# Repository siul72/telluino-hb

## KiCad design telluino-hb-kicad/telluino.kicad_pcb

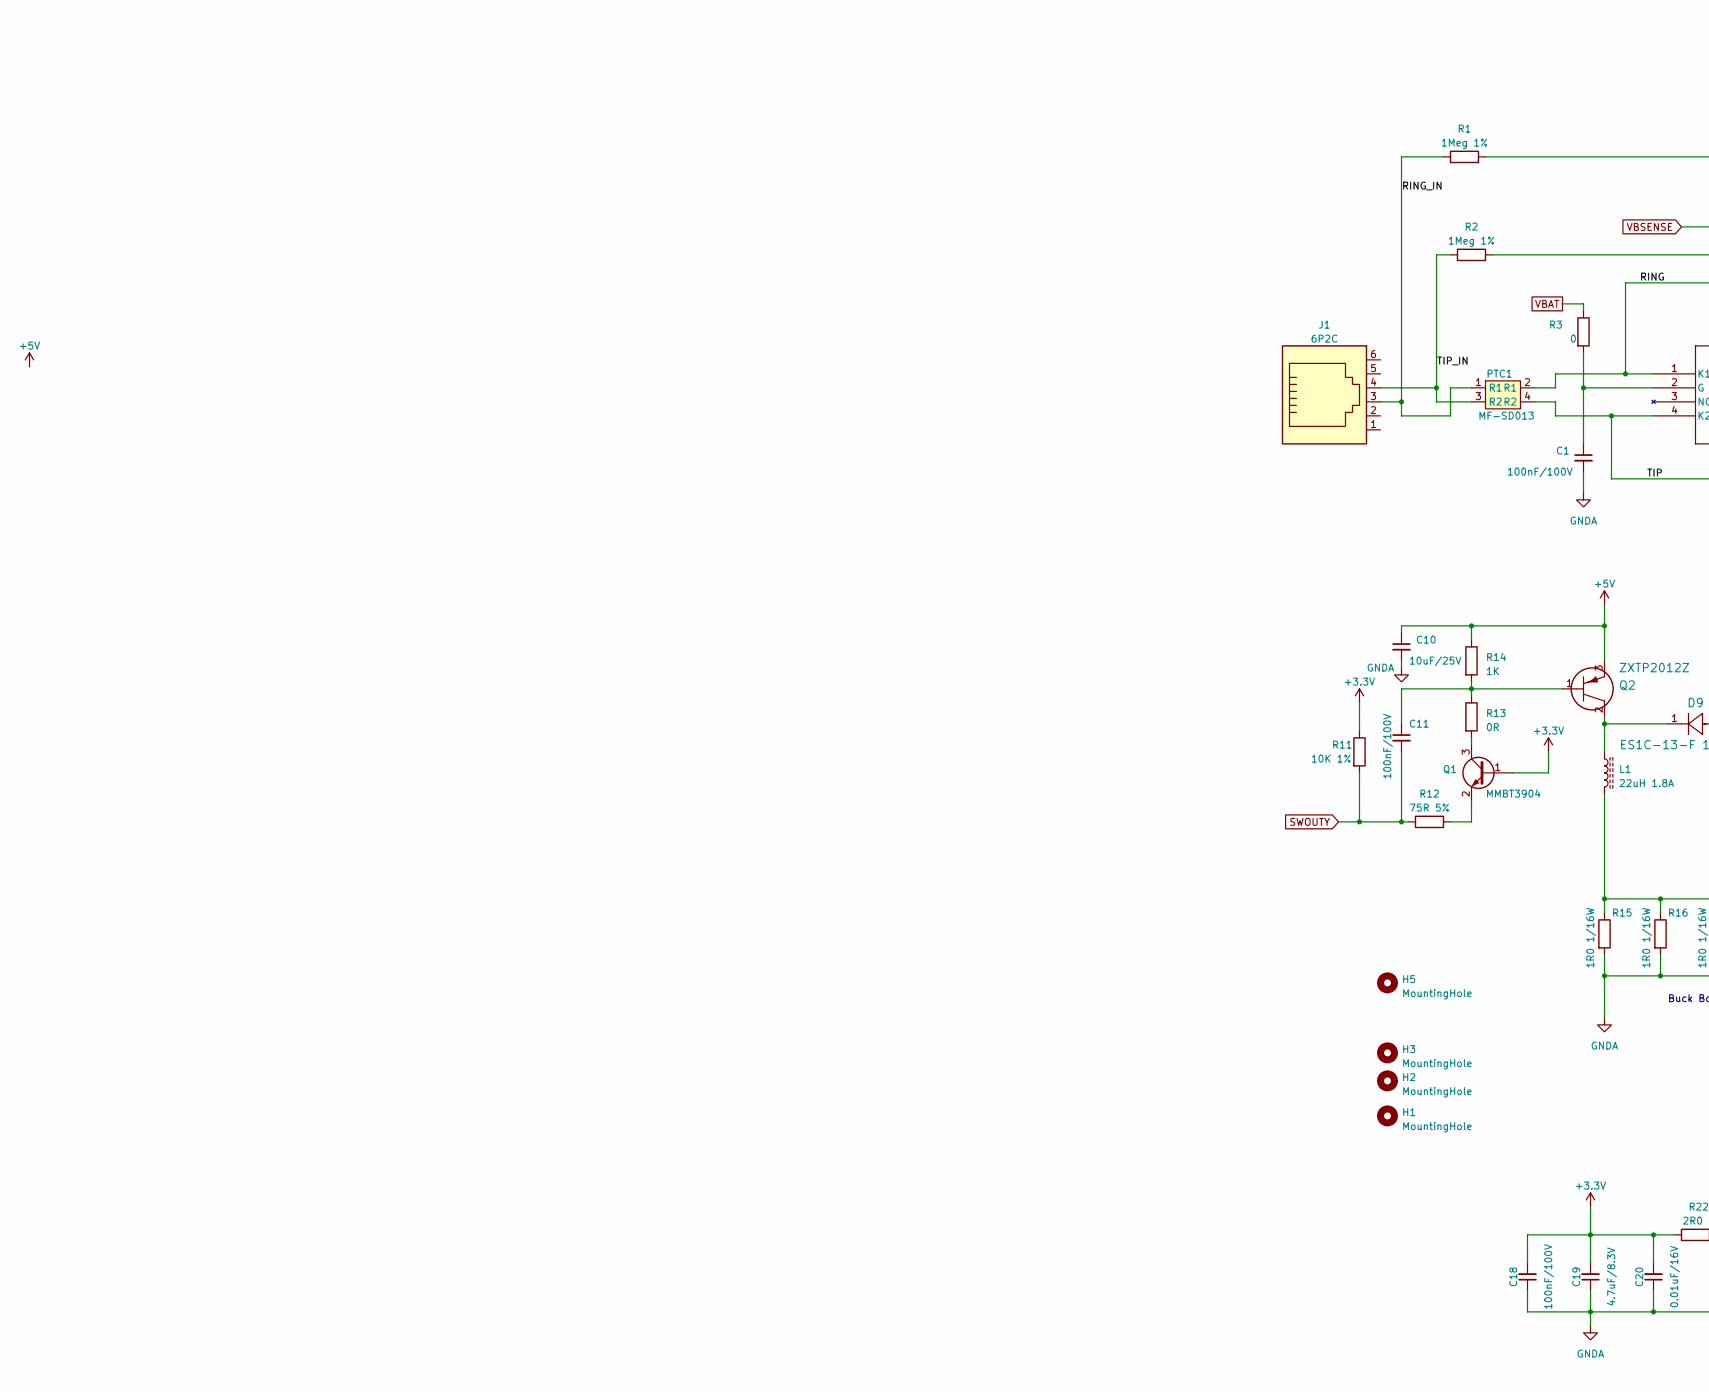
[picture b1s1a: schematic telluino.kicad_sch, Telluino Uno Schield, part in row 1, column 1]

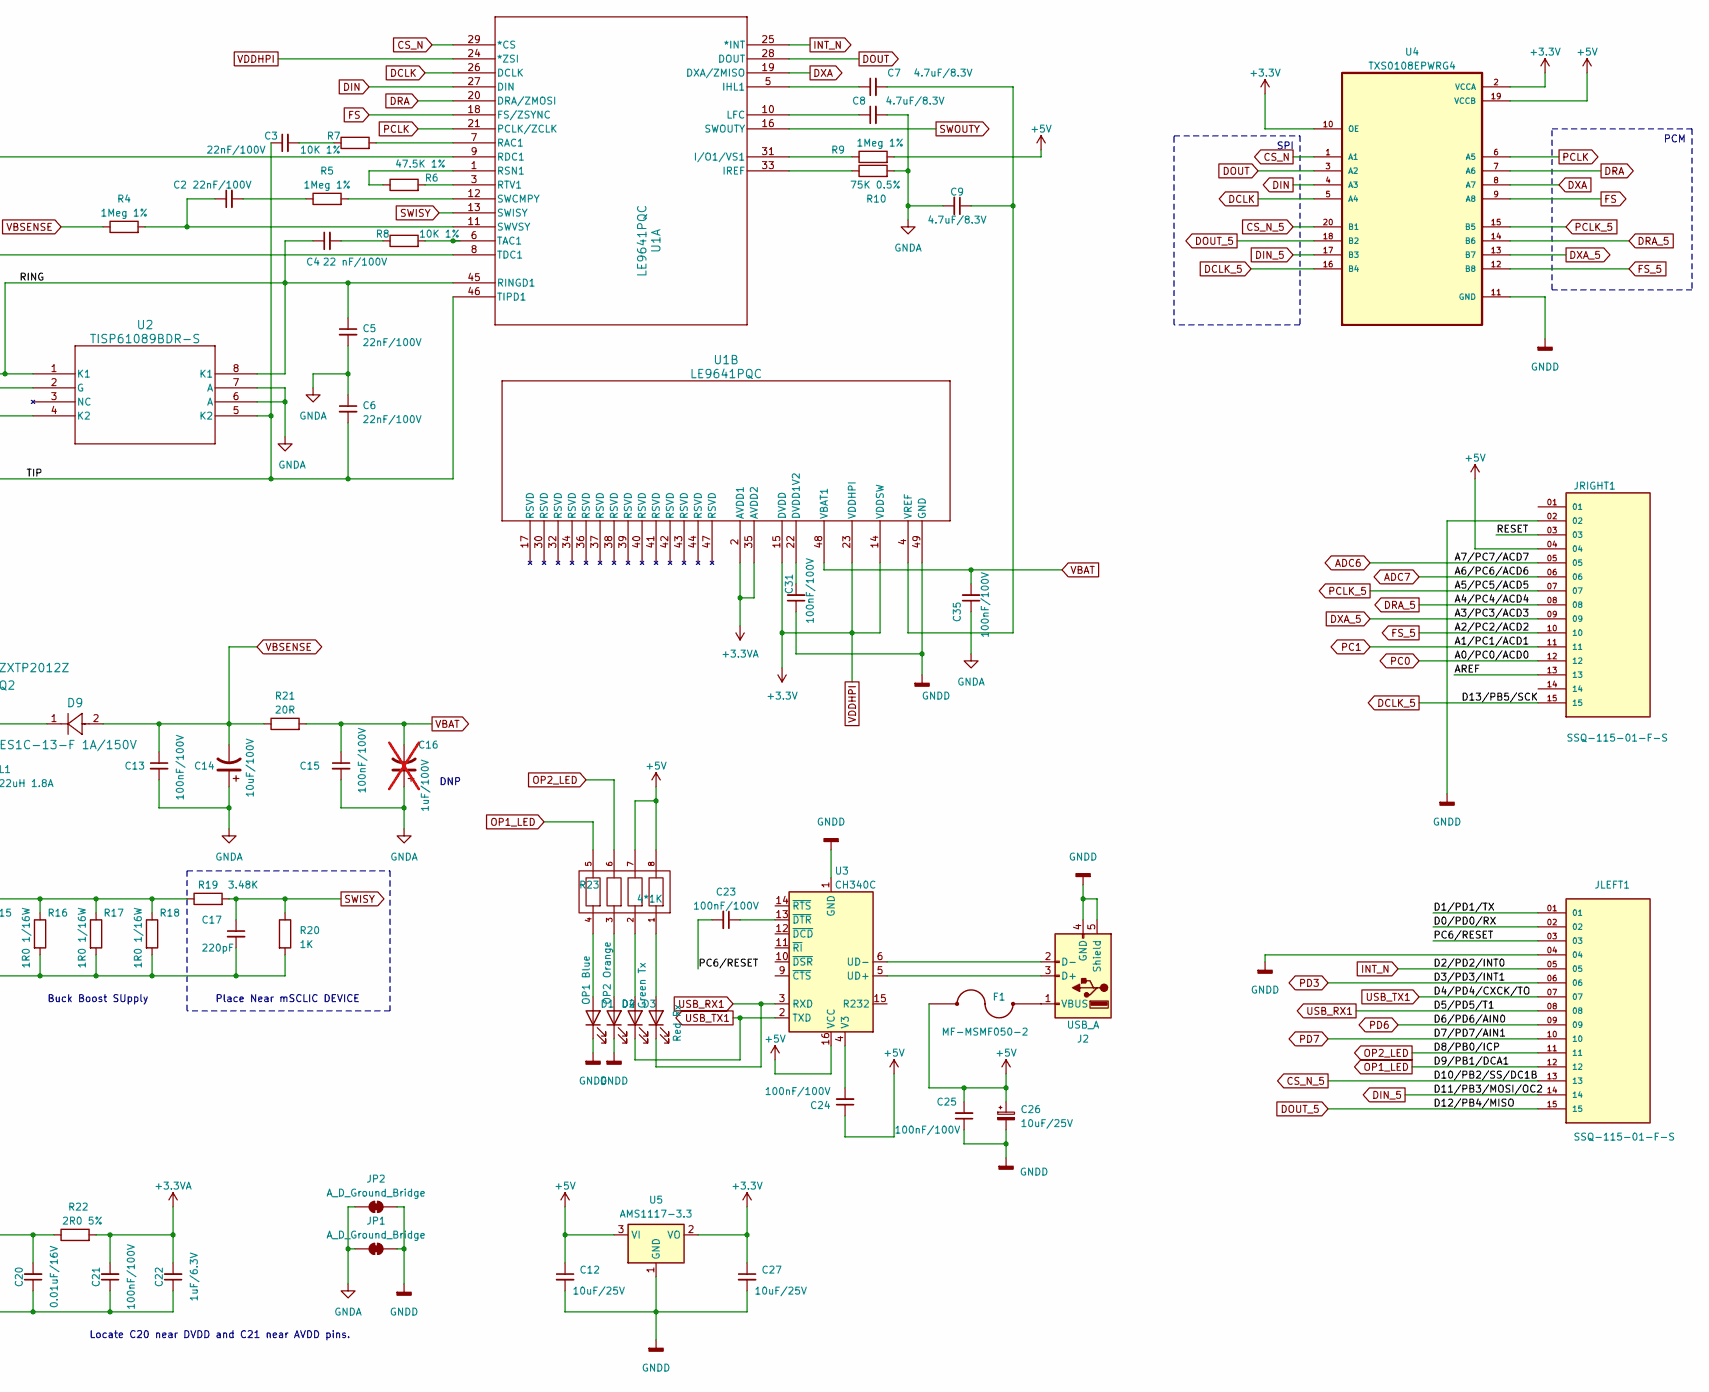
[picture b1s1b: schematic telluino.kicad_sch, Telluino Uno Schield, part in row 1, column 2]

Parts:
C1, C11, C13, C15, C18, C21, C23, C24, C25, C31, C35: 100nF/100V; C_0603_1608Metric
C2, C3, C5, C6: 22nF/100V; C_0603_1608Metric
C4: 22 nF/100V; C_0603_1608Metric
C7, C8, C9, C19: 4.7uF/8.3V; C_0603_1608Metric
C10, C12, C27: 10uF/25V; C_0603_1608Metric
C14: 10uF/100V; CP_Radial_D8.0mm_P3.50mm
C16: 1uF/100V; CP_Radial_D8.0mm_P3.50mm; not fitted
C17: 220pF; C_0603_1608Metric
C20: 0.01uF/16V; C_0603_1608Metric
C22: 1uF/6.3V; C_0603_1608Metric
C26: 10uF/25V; CP_Radial_D5.0mm_P2.50mm
D1: OP1 Blue; LED_0603_1608Metric
D2: OP2 Orange; LED_0603_1608Metric
D3: Red Rx; LED_0603_1608Metric
D4: Green Tx; LED_0603_1608Metric
D9: ES1C-13-F 1A/150V; D_SMA
F1: MF-MSMF050-2; FUSM4632X85
H1, H2, H3: MountingHole; MountingHole_4.3mm_M4
H5: MountingHole; MountingHole_2.2mm_M2
J1: 6P2C; RJ12_Amphenol_54601
J2: USB_A; USB_A_CNCTech_1001-011-01101_Horizontal
JLEFT1: SSQ-115-01-F-S; SAMTEC_SSQ-115-01-F-S; PARTREV R
JP1, JP2: A_D_Ground_Bridge; SolderJumper-2_P1.3mm_Bridged_RoundedPad1.0x1.5mm
JRIGHT1: SSQ-115-01-F-S; SAMTEC_SSQ-115-01-F-S; PARTREV R
L1: 22uH 1.8A; L_10.4x10.4_H4.8
PTC1: MF-SD013; ptc-4-mf-sd
Q1: MMBT3904; SOT-23
Q2: ZXTP2012Z; SOT-89-3_4P5X2P6_DIO
R1, R2, R4, R5, R9: 1Meg 1%; R_0603_1608Metric
R3: 0; R_0603_1608Metric
R6: 47.5K 1%; R_0603_1608Metric
R7, R8, R11: 10K 1%; R_0603_1608Metric
R10: 75K 0.5%; R_0603_1608Metric
R12: 75R 5%; R_0603_1608Metric
R13: 0R; R_0603_1608Metric
R14: 1K; R_0603_1608Metric
R15, R16, R17, R18: 1R0 1/16W; R_0402_1005Metric
R19: 3.48K; R_0402_1005Metric
R20: 1K; R_0402_1005Metric
R21: 20R; R_1206_3216Metric
R22: 2R0 5%; R_0603_1608Metric
R23: 4*1K; RESCAXE80P320X160X70-8N; PARTREV 0
U1: LE9641PQC; QFN50P700X700X90-49N
U2: TISP61089BDR-S; SOIC127P780X210-8N
U3: CH340C; SOIC-16_3.9x9.9mm_P1.27mm
U4: TXS0108EPWRG4; SOP65P640X120-20N
U5: AMS1117-3.3; SOT-223-3_TabPin2

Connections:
+3.3VA: C21.2, C22.2, R22.2, U1.2 (AVDD1), U1.35 (AVDD2)
+3.3VP: C24.2, U3.4 (V3); also elsewhere on the board
+3V3: JRIGHT1.14; also elsewhere on the board
/AREF: JRIGHT1.13
/D0/PD0/RX: JLEFT1.02
/D1/PD1/TX: JLEFT1.01
/PC6/RESET: C23.2, JLEFT1.03
/RESET: JRIGHT1.03
/RING: C4.1, C5.1, PTC1.2 (R1), U1.45 (RINGD1), U2.1 (K1), U2.8 (K1)
/RING_IN: J1.3, PTC1.1 (R1), R1.1
/TIP: C3.1, C6.2, PTC1.4 (R2), U1.46 (TIPD1), U2.4 (K2), U2.5 (K2)
/TIP_IN: J1.4, PTC1.3 (R2), R2.1
ADC6: JRIGHT1.05
ADC7: JRIGHT1.06
CS_N: U1.29 (*CS), U4.1 (A1)
CS_N_5: JLEFT1.13, U4.20 (B1)
DCLK: U1.26 (DCLK), U4.5 (A4)
DCLK_5: JRIGHT1.15, U4.16 (B4)
DIN: U1.27 (DIN), U4.4 (A3)
DIN_5: JLEFT1.14, U4.17 (B3)
DOUT: U1.28 (DOUT), U4.3 (A2)
DOUT_5: JLEFT1.15, U4.18 (B2)
DRA: U1.20 (DRA/ZMOSI), U4.7 (A6)
DRA_5: JRIGHT1.08, U4.14 (B6)
DXA: U1.19 (DXA/ZMISO), U4.8 (A7)
DXA_5: JRIGHT1.09, U4.13 (B7)
FS: U1.18 (FS/ZSYNC), U4.9 (A8)
FS_5: JRIGHT1.10, U4.12 (B8)
GNDA: C1.2, C5.2, C6.1, C8.2, C9.2, C10.2, C13.2, C14.1, C15.2, C16.1, C17.2, C18.1, C19.1, C20.1, C21.1, C22.1, C35.1, JP1.1 (A), JP2.1 (A), R10.2, R15.2, R16.2, R17.2, R18.2, R20.2, U2.6 (A), U2.7 (A)
INT_N: JLEFT1.05, U1.25 (*INT)
unnamed: C2.2, R5.1
unnamed: C3.2, R7.1
unnamed: C4.2, R8.1
unnamed 33: C11.1, Q2.1, R13.1, R14.2; also elsewhere on the board
unnamed: D1.2 (A), R23.4
unnamed: D2.2 (A), R23.3
unnamed: D3.2 (A), R23.1
unnamed: D4.2 (A), R23.2
unnamed 38: D9.1, L1.1, Q2.2; also elsewhere on the board
unnamed: J2.3 (D+), U3.5 (UD+)
unnamed: J2.2 (D-), U3.6 (UD-)
unnamed: F1.1, J2.1 (VBUS)
unnamed: L1.2, R15.1, R16.1, R17.1, R18.1, R19.1
unnamed: Q1.3 (C), R13.2
unnamed: Q1.2 (E), R12.2
unnamed: C7.1, U1.5 (IHL1)
unnamed: R10.1, U1.33 (IREF)
unnamed: R9.1, U1.31 (I/O1/VS1)
unnamed: C8.1, U1.10 (LFC)
unnamed: R7.2, U1.7 (RAC1)
unnamed: R1.2, U1.9 (RDC1)
unnamed: R6.1, U1.1 (RSN1)
unnamed: R6.2, U1.3 (RTV1)
unnamed: R5.2, U1.12 (SWCMPY)
unnamed: C2.1, R4.2, U1.11 (SWVSY)
unnamed: R8.2, U1.6 (TAC1)
unnamed: R2.2, U1.8 (TDC1)
unnamed: C31.2, U1.22 (DVDD1V2)
unnamed: C7.2, C9.1, U1.4 (VREF)
unnamed: C1.1, R3.2, U2.2 (G)
unnamed: C23.1, U3.13 (~DTR)
OP1_LED: JLEFT1.12, R23.5
OP2_LED: JLEFT1.11, R23.6
PC0: JRIGHT1.12
PC1: JRIGHT1.11
PCLK: U1.21 (PCLK/ZCLK), U4.6 (A5)
PCLK_5: JRIGHT1.07, U4.15 (B5)
PD3: JLEFT1.06
PD6: JLEFT1.09
PD7: JLEFT1.10
SWISY: C17.1, R19.2, R20.1, U1.13 (SWISY)
SWOUTY: C11.2, R11.2, R12.1, U1.16 (SWOUTY)
USB_RX1: D3.1 (K), JLEFT1.08, U3.3 (RXD)
USB_TX1: D4.1 (K), JLEFT1.07, U3.2 (TXD)
VBAT: C15.1, C16.2, C35.2, R3.1, R21.2, U1.48 (VBAT1)
VBSENSE: C13.1, C14.2, D9.2, R4.1, R21.1
VDDHPI: C18.2, C19.2, C20.2, C27.1, Q1.1 (B), R11.1, R22.1, U1.14 (VDDSW), U1.15 (DVDD), U1.23 (VDDHPI), U1.24 (*ZSI), U4.2 (VCCA), U4.10 (OE), U5.2 (VO); also elsewhere on the board

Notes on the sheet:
PCM
SPI
DNP
Locate C20 near DVDD and C21 near AVDD pins.
Buck Boost SUpply
Place Near mSCLIC DEVICE

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
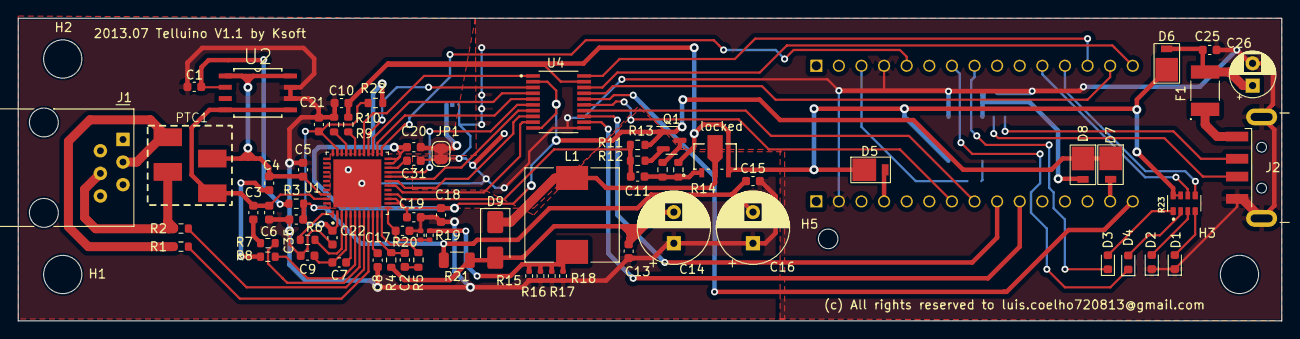
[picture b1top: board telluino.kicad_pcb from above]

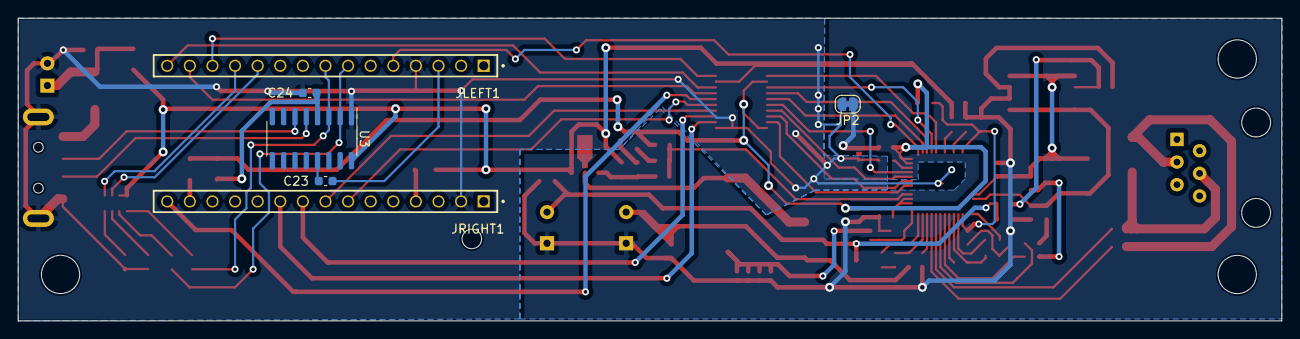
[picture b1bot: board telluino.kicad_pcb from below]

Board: 2 copper layers, 142.0 x 34.0 mm, 78 parts (6 on the bottom side), 70 nets.

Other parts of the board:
D5, D6, D7, D8: SS1P3L; DO220AAL
locked: ZXTP2012Z; SOT-89-3_4P5X2P6_DIO

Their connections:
+3.3VP: D8.2 (A); also elsewhere on the board
+3V3: D7.2 (A); also elsewhere on the board
unnamed 33: locked.1; also elsewhere on the board
unnamed 38: locked.2; also elsewhere on the board
VDDHPI: D7.1 (K), D8.1 (K); also elsewhere on the board

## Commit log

2023-06-10 base_from_telluino_v1
2023-06-10 first_routing
2023-06-11 placement done
2023-06-13 final board
2023-06-14 order_made
2023-06-15 small updates
2023-06-15 delete_backups
2023-06-16 cleanup
2023-06-24 add case 3d drawings
2023-07-03 revision after bom review and schematic review
    U1 Pin 24 to connect to VCC
    Review components to make is more affordable
2023-07-06 reworn resistor array
2023-08-25 update after first review
2023-08-25 add todo list
2023-08-27 rework 3.3 power supply
2023-09-21 update_for_next_Version
2023-09-21 update git ignore
2023-12-03 start_case_design
2023-12-04 step1
2023-12-17 case_done
2023-12-17 fix pocket
2024-12-23 latest update

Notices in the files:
telluino-hb-kicad/telluino.kicad_pcb:
(c) All rights reserved to luis.coelho720813@gmail.com
